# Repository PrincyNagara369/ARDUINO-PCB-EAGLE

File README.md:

# ARDUINO-PCB-EAGLE
The goal of the project was to create a custom Arduino board tailored to specific requirements.

I started by creating a schematic using Eagle's schematic editor. I carefully selected and placed components such as the microcontroller, capacitors, resistors, and other necessary peripherals. I made sure to establish proper connections between the components, considering factors like signal integrity and power distribution.

After completing the schematic, I switched to the PCB layout view in Eagle. I defined the board outline and positioned the components, ensuring an efficient and compact design. I paid attention to routing the connections, avoiding unnecessary overlaps or crossings. Additionally, I incorporated copper pours for power and ground planes to improve signal integrity and reduce noise.

Throughout the design process, I followed industry-standard design guidelines and performed a thorough Design Rule Check (DRC) to identify and rectify any errors or violations. I also generated the necessary Gerber files required for manufacturing, adhering to the specifications provided by the manufacturer.

Overall, this project allowed me to showcase my proficiency in Eagle software, PCB design principles, and attention to detail. It was a valuable learning experience, and I am proud of the final design outcome.

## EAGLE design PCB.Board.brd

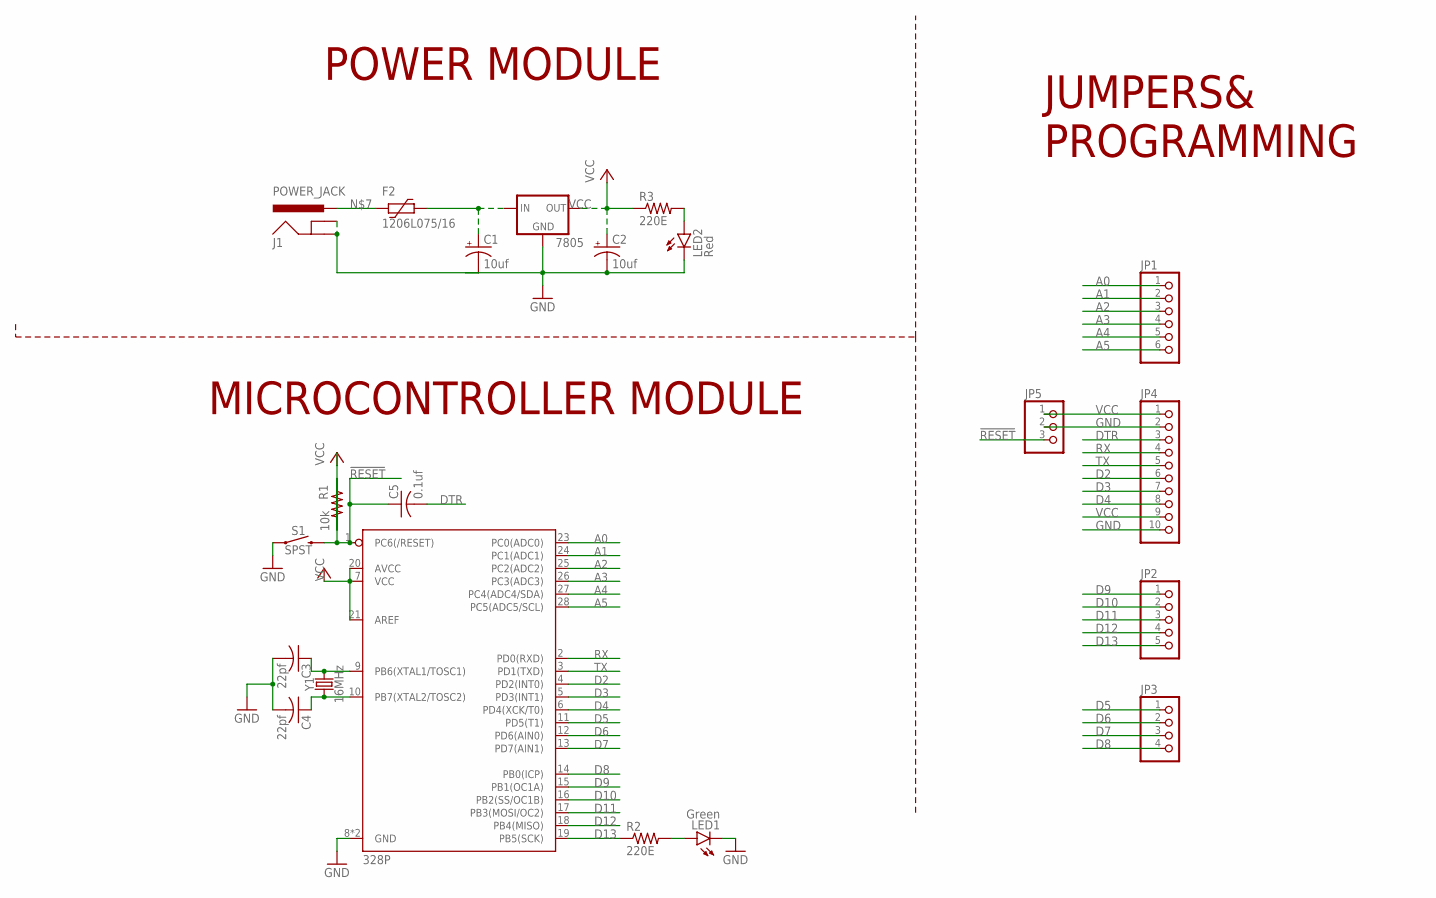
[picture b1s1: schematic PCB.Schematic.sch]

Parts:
C1, C2: 10uf; E2,5-6E
C3, C4: 22pf; C025-024X044
C5: 0.1uf; C025-024X044
F2: 1206L075/16; 1206L
J1: POWER_JACK; POWER_JACK_PTH
JP1: PINHD-1X6; 1X06
JP2: PINHD-1X5; 1X05
JP3: PINHD-1X4; 1X04
JP4: PINHD-1X10; 1X10
JP5: PINHD-1X3; 1X03
LED1: Green; LED3MM
LED2: Red; LED3MM
R1: 10k; 0204/7
R2, R3: 220E; 0204/7
S1: SPST; TACTILE_SWITCH_PTH_6.0MM
U1: 7805; 78XXS
U2: 328P; DIP28
Y1: 16MHz; HC49US

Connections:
!RESET: C5.1, JP5.3, R1.1, S1.3 (2), U2.1 (PC6(/RESET))
A0: JP1.1, U2.23 (PC0(ADC0))
A1: JP1.2, U2.24 (PC1(ADC1))
A2: JP1.3, U2.25 (PC2(ADC2))
A3: JP1.4, U2.26 (PC3(ADC3))
A4: JP1.5, U2.27 (PC4(ADC4/SDA))
A5: JP1.6, U2.28 (PC5(ADC5/SCL))
D2: JP4.6, U2.4 (PD2(INT0))
D3: JP4.7, U2.5 (PD3(INT1))
D4: JP4.8, U2.6 (PD4(XCK/T0))
D5: JP3.1, U2.11 (PD5(T1))
D6: JP3.2, U2.12 (PD6(AIN0))
D7: JP3.3, U2.13 (PD7(AIN1))
D8: JP3.4, U2.14 (PB0(ICP))
D9: JP2.1, U2.15 (PB1(OC1A))
D10: JP2.2, U2.16 (PB2(SS/OC1B))
D11: JP2.3, U2.17 (PB3(MOSI/OC2))
D12: JP2.4, U2.18 (PB4(MISO))
D13: JP2.5, R2.1, U2.19 (PB5(SCK))
DTR: C5.2, JP4.3
GND: C1.-, C2.-, C3.2, C4.2, J1.GND, J1.GNDBREAK, JP4.2, JP4.10, JP5.2, LED1.K (C), LED2.K (C), S1.1, U1.GND, U2.8 (GND), U2.22 (GND)
unnamed: C1.+, F2.1, U1.IN
unnamed: C3.1, U2.9 (PB6(XTAL1/TOSC1)), Y1.2
unnamed: C4.1, U2.10 (PB7(XTAL2/TOSC2)), Y1.1
unnamed: LED1.A, R2.2
unnamed: LED2.A, R3.2
unnamed: F2.2, J1.PWR
RX: JP4.4, U2.2 (PD0(RXD))
TX: JP4.5, U2.3 (PD1(TXD))
VCC: C2.+, JP4.1, JP4.9, JP5.1, R1.2, R3.1, U1.OUT, U2.7 (VCC), U2.20 (AVCC), U2.21 (AREF)

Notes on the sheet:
POWER MODULE
JUMPERS& PROGRAMMING
MICROCONTROLLER MODULE

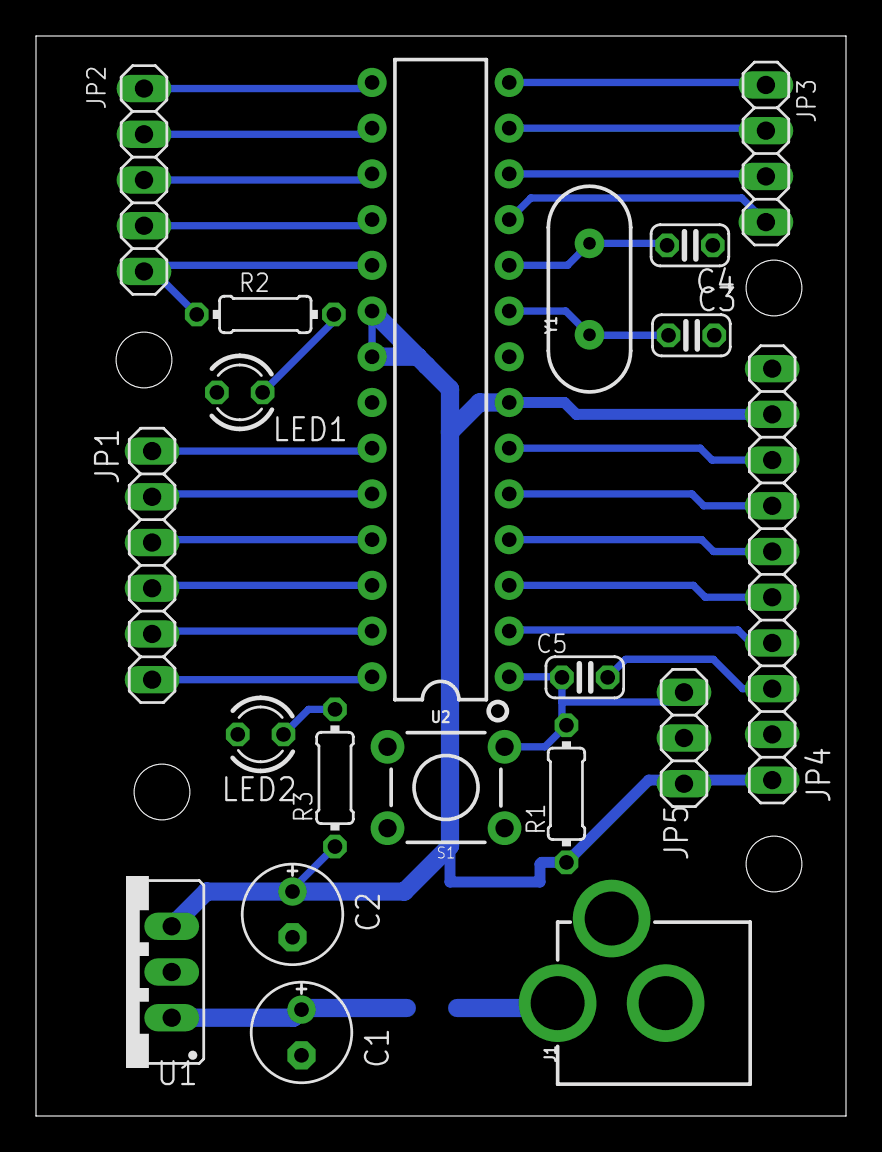
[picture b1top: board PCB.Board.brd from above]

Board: 2 copper layers, 45.0 x 60.0 mm, 21 parts (1 on the bottom side), 30 nets.

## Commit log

2023-08-27 README.md

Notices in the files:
parts and their libraries:
SparkFun-Connectors: Licensing: Creative Commons ShareAlike 4.0 International - https://creativecommons.org/licenses/by-sa/4.0
